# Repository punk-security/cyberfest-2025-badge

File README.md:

# This is the repo for the CyberNorth CyberFest badge

**This badge was given out at CyberFest conference to all attendees, and had a compass mode so you can always find your way North**

This badge uses UV full colour silk, and we ordered them from JLCPCB using EasyEDA. The PCB was built first with AutoCAD EAGLE, then exported, and imported into EasyEDA by JLCPCB for design updates. We have provided the EasyEDA exports in case you want to import and tweak the designs, or you can order your own as-is using the gerber files :)

Unlike almost all of our other badges, we ordered these partialy assembled. This means that JLCPCB placed some parts for us. We did this as the 3-axis magnometer (which does the compass reading) was tiny and needed a super tiny capacitor too!

Lots of things in this repo:

- EAGLE.brd: The AutoCAD Eagle board design
- EAGLE.sch - The AutoCAD Eagle circuit schematic
- cyberfest-2025.epro - The EasyEDA export, including the front art
- gerber.zip: the file you can upload to JLCPCB and order your own badge, as is
- firmware.ino: the arduino code that powers the badge, which you can modify and flash via the SAO connector

## Bill Of Materials

We sourced some parts direct from JLCPCB, so you may need to tweak footprints when ordering direct. The most notable difference is the coin cell battery clasp, which has smaller "foot" pads. The one provided by JLC was awful and we would recommend replacing it.

Essentially its:

* ATTINY412 microcontroller
* Button - any surface mount button fitting the footprint will work
* CR2032 battery clip  - surface mount not through hole
* Neopixel 5050 addressable LED - Definitely get the right version of these
* LIS2MDLTR - a 3-axis magnetometer (the compass)

## How does it work?

The badge does the usually blinky modes, but also provides a north bearing. To do this, we read the magentic readings from a 3-axis magnometer (LIS2MDLTR)

Compass reading is difficult, as the enviroment is full of intereference. We need to calibrate our readings, so when compass mode is activated we take continous readings for a few seconds. During this time, you should rotate the badge a few times. 

You'll see lots of really tricky code in this repo around compass bearings. Essentially turning magentic readings into a bearing is difficult, and the math to do it takes a lot of flash space. More flash space then we have available actually, so we had to do some funky coding to get a near-enough reading. Our resolution is one of 8 LEDS, so it's a fair trade off!

The current build uses 4082 of 4096 bytes of flash!

## Ordering your own badge

We've uploaded the AutoCAD EAGLE schematic and board design!  You will probably have to do some tweaks to get it working as they're not designed to be standalone exports.

This is then exported to EasyEDA to add the colour print to the boards. The file for that is already in the repo, so you can skip the EAGLE step if you prefer.

We've also uploaded the gerber.zip.  Take this to JLCPCB and you can order your own exact copies of the board :)

## Writing and flashing code!

We use [MegaTinyCore](https://github.com/SpenceKonde/megaTinyCore) for the arduino interface for ATTINY4x2 chips.

Dev and flashing is done within the Arduino IDE ( < v2 ) using a jtag2updi interface, as discussed [here](https://github.com/SpenceKonde/AVR-Guidance/blob/master/UPDI/jtag2updi.md)

We use [these little usb sticks](https://amzn.eu/d/c0lx0wG), with a 4.7k resistor soldered between the Tx and Rx lines.  

### Installing MegaTinyCore dependencies

This board package can be installed via the board manager in arduino. The boards manager URL is:

`http://drazzy.com/package_drazzy.com_index.json`

1. File -> Preferences, enter the above URL in "Additional Boards Manager URLs"
2. Tools -> Boards -> Boards Manager...
3. Wait while the list loads (takes longer than one would expect, and refreshes several times).
4. Select "megaTinyCore by Spence Konde" and click "Install". For best results, choose the most recent version.

### Setting up the IDE

1. Open the file **firmware.ino** in arduino
2. Select tools > Board > megaTinyCore > ATtiny412/402/212/202
3. Select tools > Chip > ATtiny412
4. Select tools > Clock > 16Mhz internal *(we get power issues otherwise)*
5. Select tools > millis > Disabled
5. Select tools > Programmer > SerialUPDI SLOW
6. Select tools > Port > ( pick your COM port)

### Flashing firmware
1. Connect the 3v3 pin to 3v on your usb (maybe wedge it in the battery clip)
2. Connect GND to GND
3. Connect UPDI to the RxD port
4. Click Upload button

## How to solder?

Make sure to line up the dot on the attiny412 with the dot on the board.

*It's much easier if you hold the component in place with one hand, and then solder one pad. Now you can solder the rest of the pads with one hand*

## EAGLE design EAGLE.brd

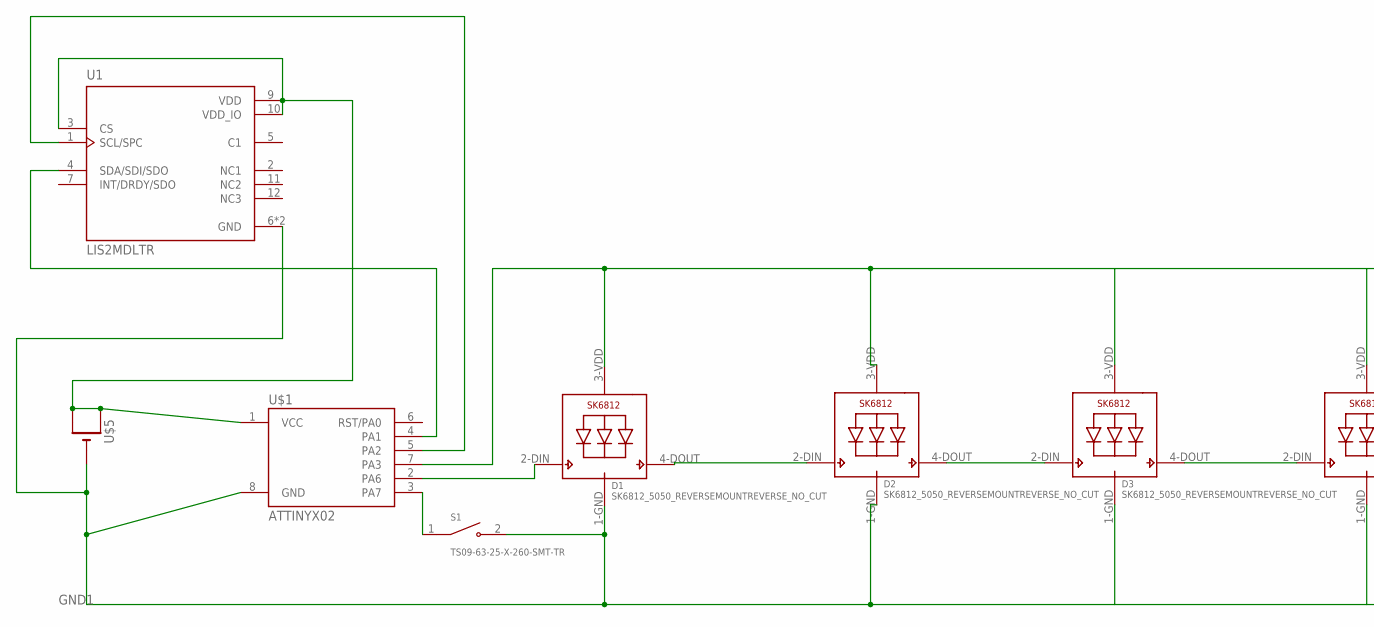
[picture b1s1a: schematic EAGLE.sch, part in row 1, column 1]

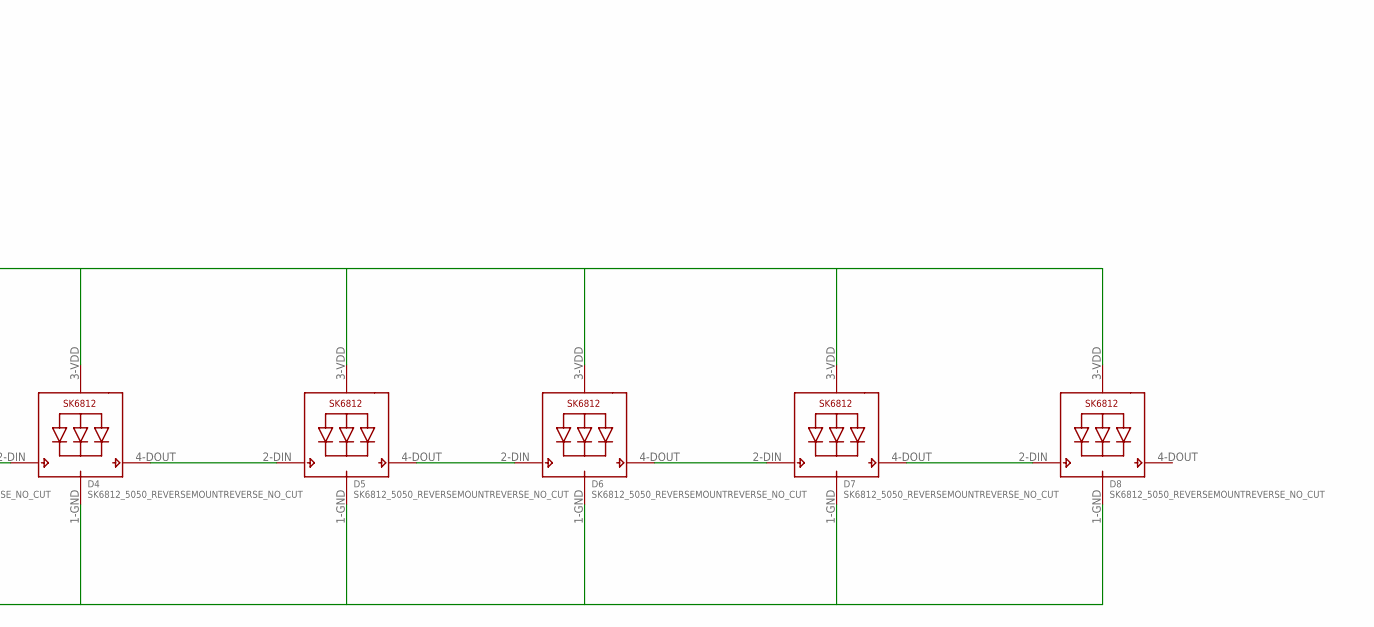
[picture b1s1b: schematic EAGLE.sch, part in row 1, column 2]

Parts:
D1, D2, D3, D4, D5, D6, D7, D8: SK6812_5050_REVERSEMOUNTREVERSE_NO_CUT; SK6812_REVERSE_NO_CUT
S1: TS09-63-25-X-260-SMT-TR; SW_TS09-63-25-X-260-SMT-TR
U1: LIS2MDLTR; PQFN50P200X200X70-12N
U$1: ATTINYX02; SOIC08_JEDEC_150MIL
U$5: CR2032SMT; CR2032-SMD

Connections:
GND1: D1.1-GND (GND), D2.1-GND (GND), D3.1-GND (GND), D4.1-GND (GND), D5.1-GND (GND), D6.1-GND (GND), D7.1-GND (GND), D8.1-GND (GND), S1.2, U1.6 (GND), U1.8 (GND), U$1.8 (GND), U$5.-
unnamed: D1.4-DOUT (DO), D2.2-DIN (DI)
unnamed: D1.2-DIN (DI), U$1.2 (PA6)
unnamed: D3.4-DOUT (DO), D4.2-DIN (DI)
unnamed: D2.4-DOUT (DO), D3.2-DIN (DI)
unnamed: S1.1, U$1.3 (PA7)
unnamed: D4.4-DOUT (DO), D5.2-DIN (DI)
unnamed: D6.4-DOUT (DO), D7.2-DIN (DI)
unnamed: D7.4-DOUT (DO), D8.2-DIN (DI)
unnamed: D5.4-DOUT (DO), D6.2-DIN (DI)
unnamed: U1.1 (SCL/SPC), U$1.5 (PA2)
unnamed: U1.4 (SDA/SDI/SDO), U$1.4 (PA1)
VCC1: U1.3 (CS), U1.9 (VDD), U1.10 (VDD_IO), U$1.1 (VCC), U$5.+$1 (+), U$5.+$2 (+1)
VDD2: D1.3-VDD (VDD), D2.3-VDD (VDD), D3.3-VDD (VDD), D4.3-VDD (VDD), D5.3-VDD (VDD), D6.3-VDD (VDD), D7.3-VDD (VDD), D8.3-VDD (VDD), U$1.7 (PA3)

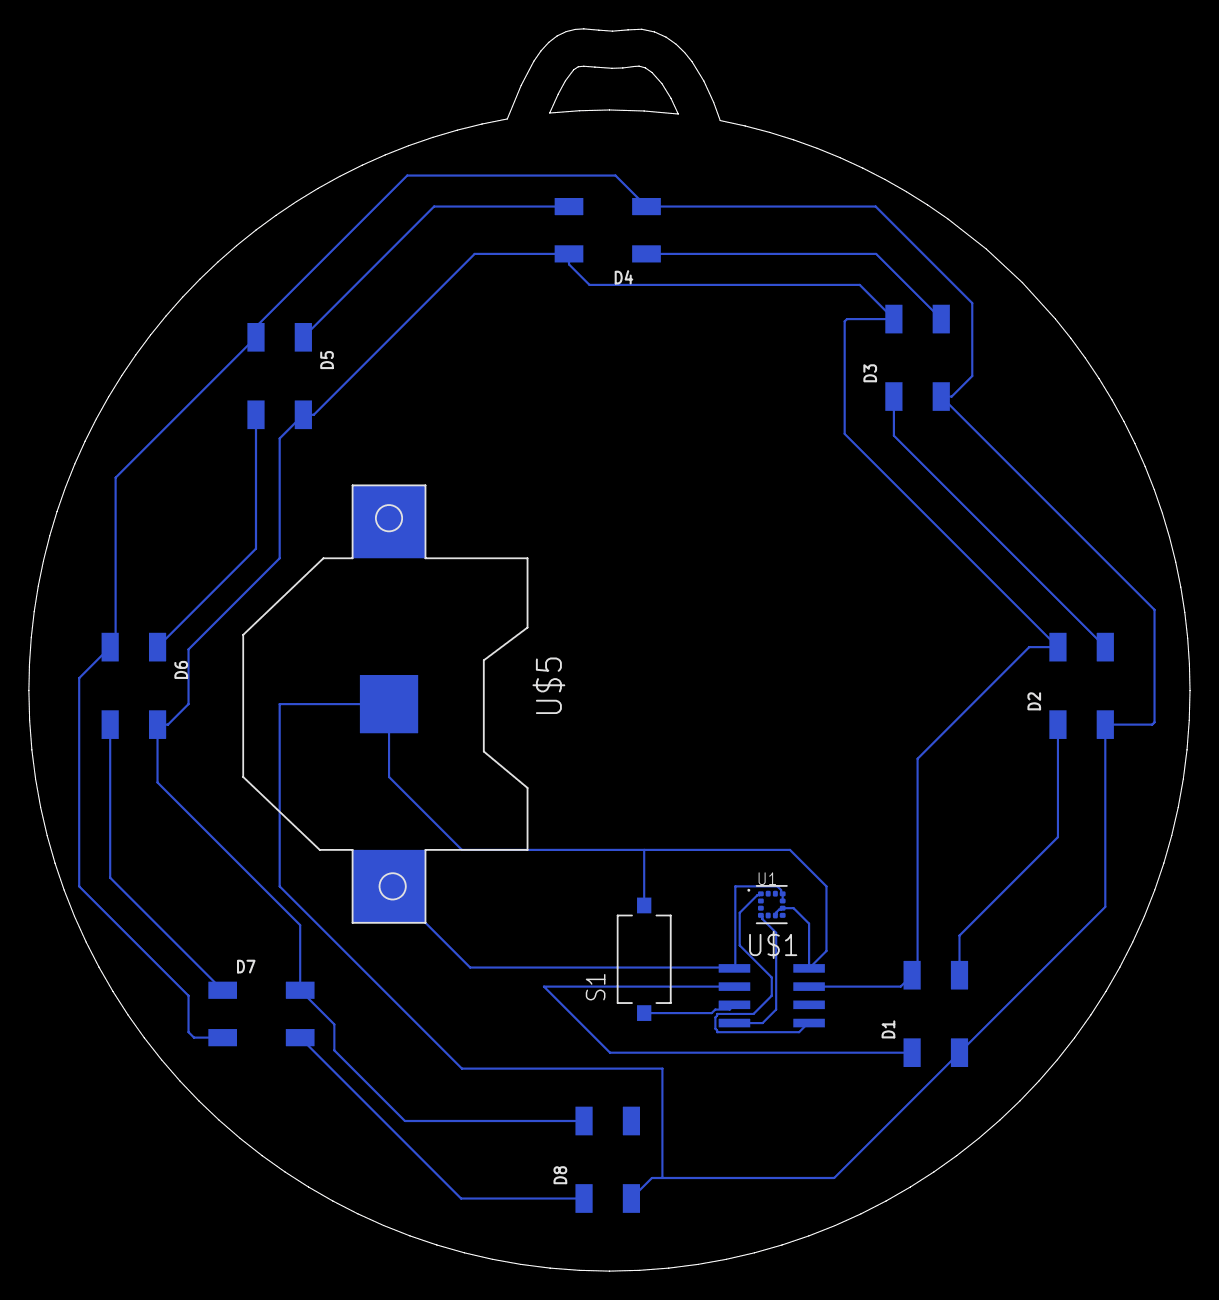
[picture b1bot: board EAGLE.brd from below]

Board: 2 copper layers, 80.9 x 86.6 mm, 12 parts (12 on the bottom side), 14 nets.

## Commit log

2025-11-02 feat: init
2025-11-02 Update firmware file name in README
